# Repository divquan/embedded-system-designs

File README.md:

# embedded-system-designs
This repository contains designs for embedded systems, including schematics, PCB layouts, and fabrication files. Ideal for learning and project inspiration.
# Embedded Systems Design Repository

Welcome to the Embedded Systems Design Repository! This repository contains a comprehensive collection of designs for various embedded systems, including detailed schematics, layouts, and printed circuit board (PCB) designs. Whether you're a beginner looking to learn more about embedded systems or an experienced developer seeking inspiration and reference designs, this repository has something for you.

## Repository Contents

1. **Schematics**
   - Detailed circuit diagrams for different embedded systems projects.
   - Includes component lists, connection details, and annotations to facilitate easy understanding and replication.

2. **PCB Layouts**
   - High-quality PCB layouts ready for fabrication.
   - Gerber files, drill files, and board outlines provided for each project.
   - Layered designs with clear routing paths, power planes, and signal integrity considerations.

3. **Project Documentation**
   - Comprehensive documentation for each project, including design goals, system architecture, and implementation details.
   - Step-by-step guides on assembling and testing the embedded systems.
   - Troubleshooting tips and common issues faced during the development process.

4. **Component Libraries**
   - Custom component libraries for popular PCB design software (e.g., Eagle, KiCad).
   - Includes footprints, 3D models, and symbol libraries for easy integration into your designs.

5. **Example Projects**
   - A variety of example projects demonstrating different aspects of embedded systems design.
   - Projects range from simple microcontroller-based designs to complex multi-component systems.
   - Examples include IoT devices, sensor networks, robotics controllers, and more.

6. **Design Resources**
   - Links to useful resources, such as datasheets, application notes, and design guidelines.
   - Tutorials and educational material to help you get started with embedded systems design.

## How to Use

- **Browse the Projects:** Explore the various projects listed in the repository. Each project folder contains all necessary files and documentation.
- **Clone the Repository:** Use `git clone` to download the repository to your local machine.
- **Open and Modify Designs:** Use your preferred PCB design software to open and modify the schematics and PCB layouts.
- **Fabricate and Assemble:** Use the provided Gerber files to fabricate your PCBs. Follow the assembly guides to build and test your embedded systems.
- **Contribute:** Feel free to contribute to the repository by adding your own designs, improving existing ones, or providing feedback and suggestions.

We hope this repository serves as a valuable resource for your embedded systems design projects. Happy designing!

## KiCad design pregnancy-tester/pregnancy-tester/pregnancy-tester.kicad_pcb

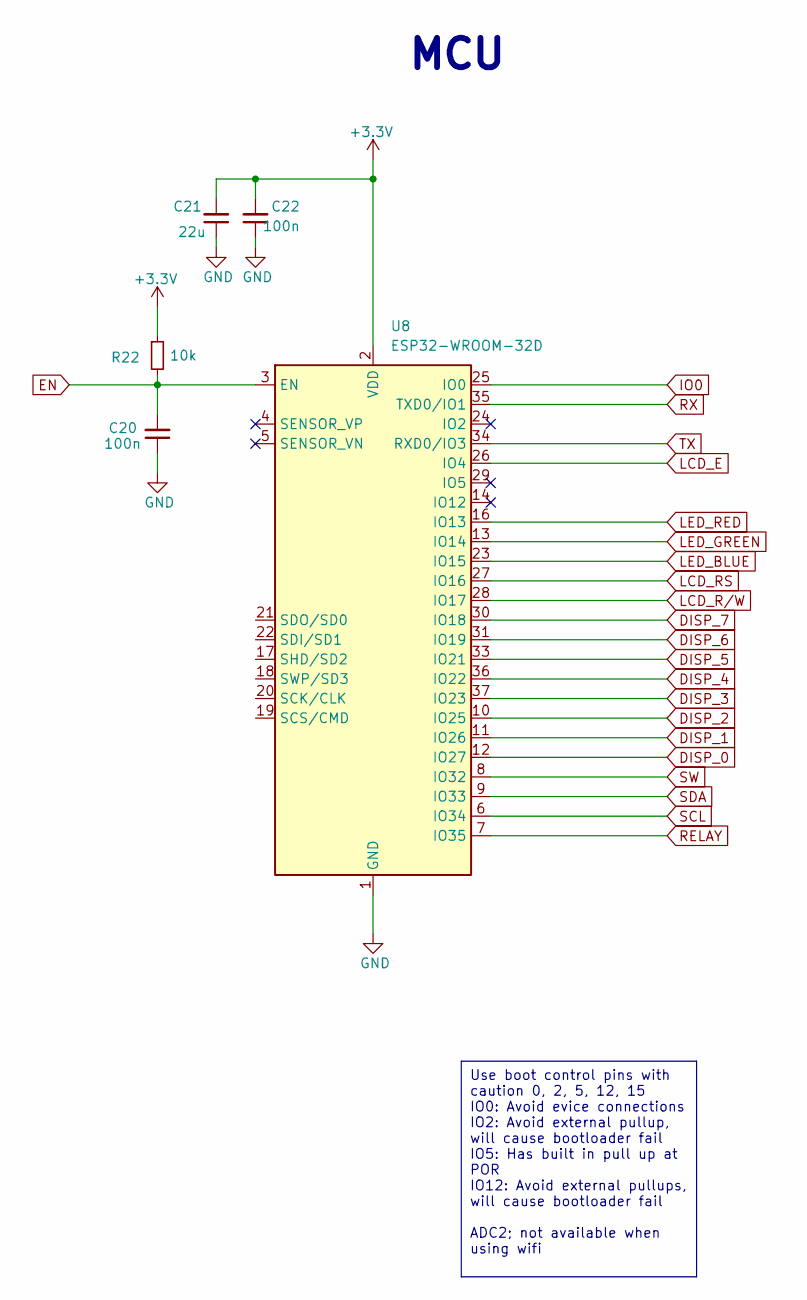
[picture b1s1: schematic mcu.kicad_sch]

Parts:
C20, C22: 100n; C_0201_0603Metric_Pad0.64x0.40mm_HandSolder
C21: 22u; C_01005_0402Metric_Pad0.57x0.30mm_HandSolder
R22: 10k; R_01005_0402Metric_Pad0.57x0.30mm_HandSolder
U8: ESP32-WROOM-32D

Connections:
+3.3V: C20.1, C21.1, C21.2, C22.1, C22.2, R22.1, U8.1 (GND), U8.2 (VDD), U8.15 (GND), U8.38 (GND), U8.39 (GND); also elsewhere on the board
DISP_0: U8.12 (IO27); also elsewhere on the board
DISP_1: U8.11 (IO26); also elsewhere on the board
DISP_2: U8.10 (IO25); also elsewhere on the board
DISP_3: U8.37 (IO23); also elsewhere on the board
DISP_4: U8.36 (IO22); also elsewhere on the board
DISP_5: U8.33 (IO21); also elsewhere on the board
DISP_6: U8.31 (IO19); also elsewhere on the board
DISP_7: U8.30 (IO18); also elsewhere on the board
EN: C20.2, R22.2, U8.3 (EN); also elsewhere on the board
IO0: U8.25 (IO0); also elsewhere on the board
LCD_E: U8.26 (IO4); also elsewhere on the board
LCD_RS: U8.27 (IO16); also elsewhere on the board
LCD_R/W: U8.28 (IO17); also elsewhere on the board
LED_BLUE: U8.23 (IO15)
LED_GREEN: U8.13 (IO14)
LED_RED: U8.16 (IO13)
RELAY: U8.7 (IO35); also elsewhere on the board
RX: U8.35 (TXD0/IO1); also elsewhere on the board
SCL: U8.6 (IO34); also elsewhere on the board
SDA: U8.9 (IO33); also elsewhere on the board
SW: U8.8 (IO32); also elsewhere on the board
TX: U8.34 (RXD0/IO3); also elsewhere on the board

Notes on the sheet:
Use boot control pins with caution 0, 2, 5, 12, 15 IO0: Avoid evice connections IO2: Avoid external pullup, will cause bootloader fail IO5: Has built in pull up at POR IO12: Avoid external pullups, will cause bootloader fail ADC2; not available when using wifi
MCU

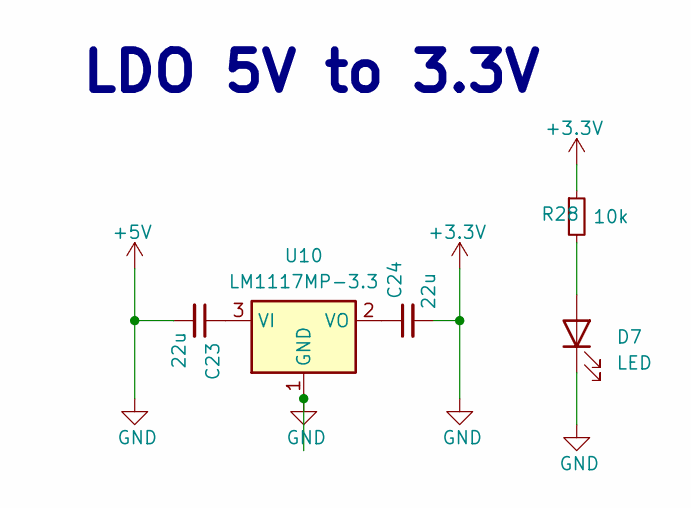
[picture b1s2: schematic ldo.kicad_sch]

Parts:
C23, C24: 22u; C_01005_0402Metric_Pad0.57x0.30mm_HandSolder
D7: LED; LED_0603_1608Metric_Pad1.05x0.95mm_HandSolder
R28: 10k; R_01005_0402Metric_Pad0.57x0.30mm_HandSolder
U10: LM1117MP-3.3; SOT-223-3_TabPin2

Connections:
+3.3V: C23.2, C24.2, D7.1 (K), R28.1, U10.1 (GND); also elsewhere on the board
unnamed: D7.2 (A), R28.2
unnamed: C23.1, U10.3 (VI)
unnamed: C24.1, U10.2 (VO)

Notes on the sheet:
LDO 5V to 3.3V

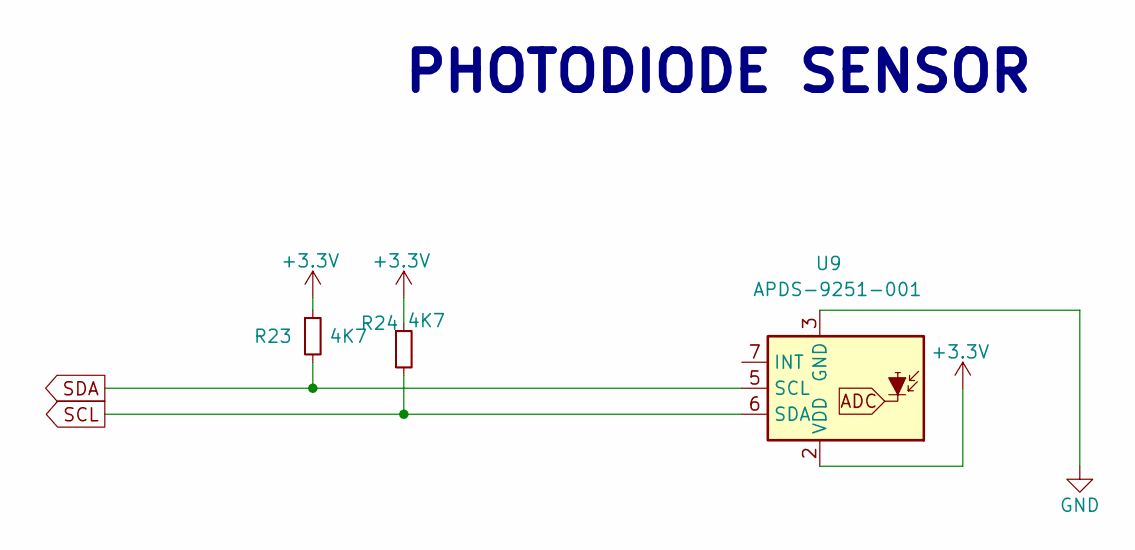
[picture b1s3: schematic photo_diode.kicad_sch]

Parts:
R23, R24: 4K7; R_01005_0402Metric_Pad0.57x0.30mm_HandSolder
U9: APDS-9251-001; Broadcom_LGA-8_2x2mm_P0.5mm

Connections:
+3.3V: R23.1, R24.1, U9.2 (VDD), U9.3 (GND); also elsewhere on the board
SCL: R24.2, U9.6 (SDA); also elsewhere on the board
SDA: R23.2, U9.5 (SCL); also elsewhere on the board

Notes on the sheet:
PHOTODIODE SENSOR

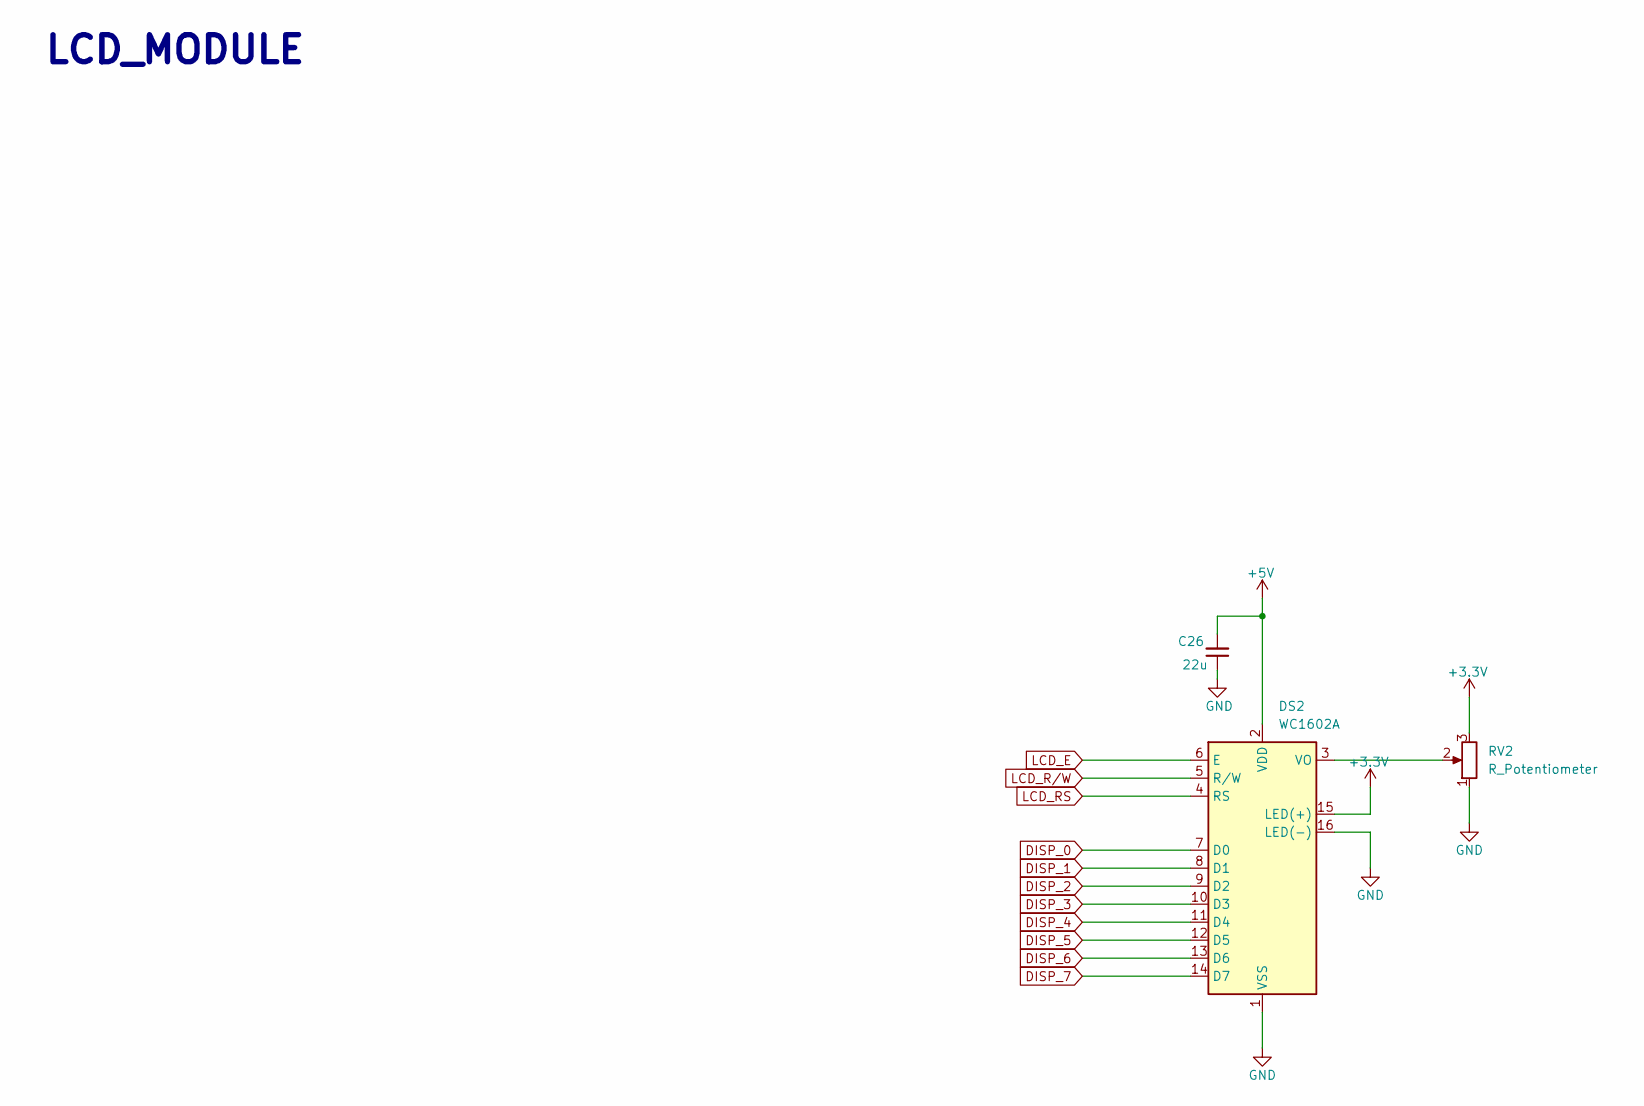
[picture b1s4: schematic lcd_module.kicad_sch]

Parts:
C26: 22u; C_01005_0402Metric_Pad0.57x0.30mm_HandSolder
DS2: WC1602A
RV2: R_Potentiometer; Potentiometer_ACP_CA14-VSMD_Vertical_Hole

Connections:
+3.3V: C26.1, C26.2, DS2.1 (VSS), DS2.2 (VDD), DS2.15 (LED(+)), DS2.16 (LED(-)), RV2.1, RV2.3; also elsewhere on the board
DISP_0: DS2.7 (D0); also elsewhere on the board
DISP_1: DS2.8 (D1); also elsewhere on the board
DISP_2: DS2.9 (D2); also elsewhere on the board
DISP_3: DS2.10 (D3); also elsewhere on the board
DISP_4: DS2.11 (D4); also elsewhere on the board
DISP_5: DS2.12 (D5); also elsewhere on the board
DISP_6: DS2.13 (D6); also elsewhere on the board
DISP_7: DS2.14 (D7); also elsewhere on the board
LCD_E: DS2.6 (E); also elsewhere on the board
LCD_RS: DS2.4 (RS); also elsewhere on the board
LCD_R/W: DS2.5 (R/W); also elsewhere on the board
unnamed: DS2.3 (VO), RV2.2

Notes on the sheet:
LCD_MODULE

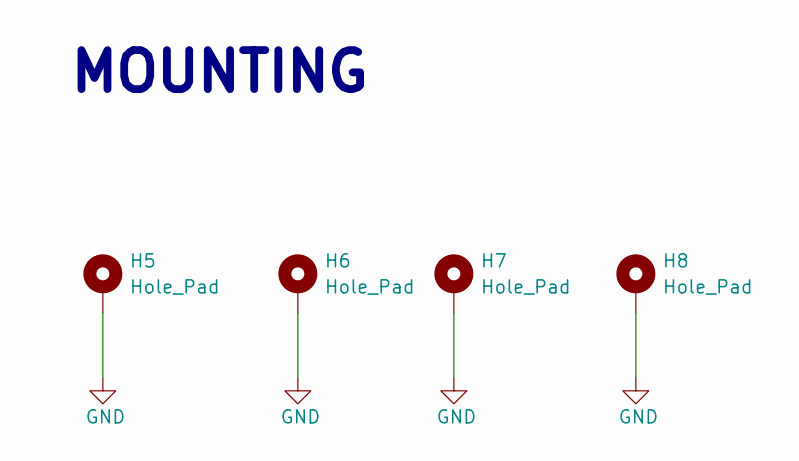
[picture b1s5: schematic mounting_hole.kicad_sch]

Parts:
H5, H6, H7, H8: Hole_Pad; MountingHole_2.2mm_M2_DIN965_Pad

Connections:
+3.3V: H5.1, H6.1, H7.1, H8.1; also elsewhere on the board

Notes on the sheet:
MOUNTING

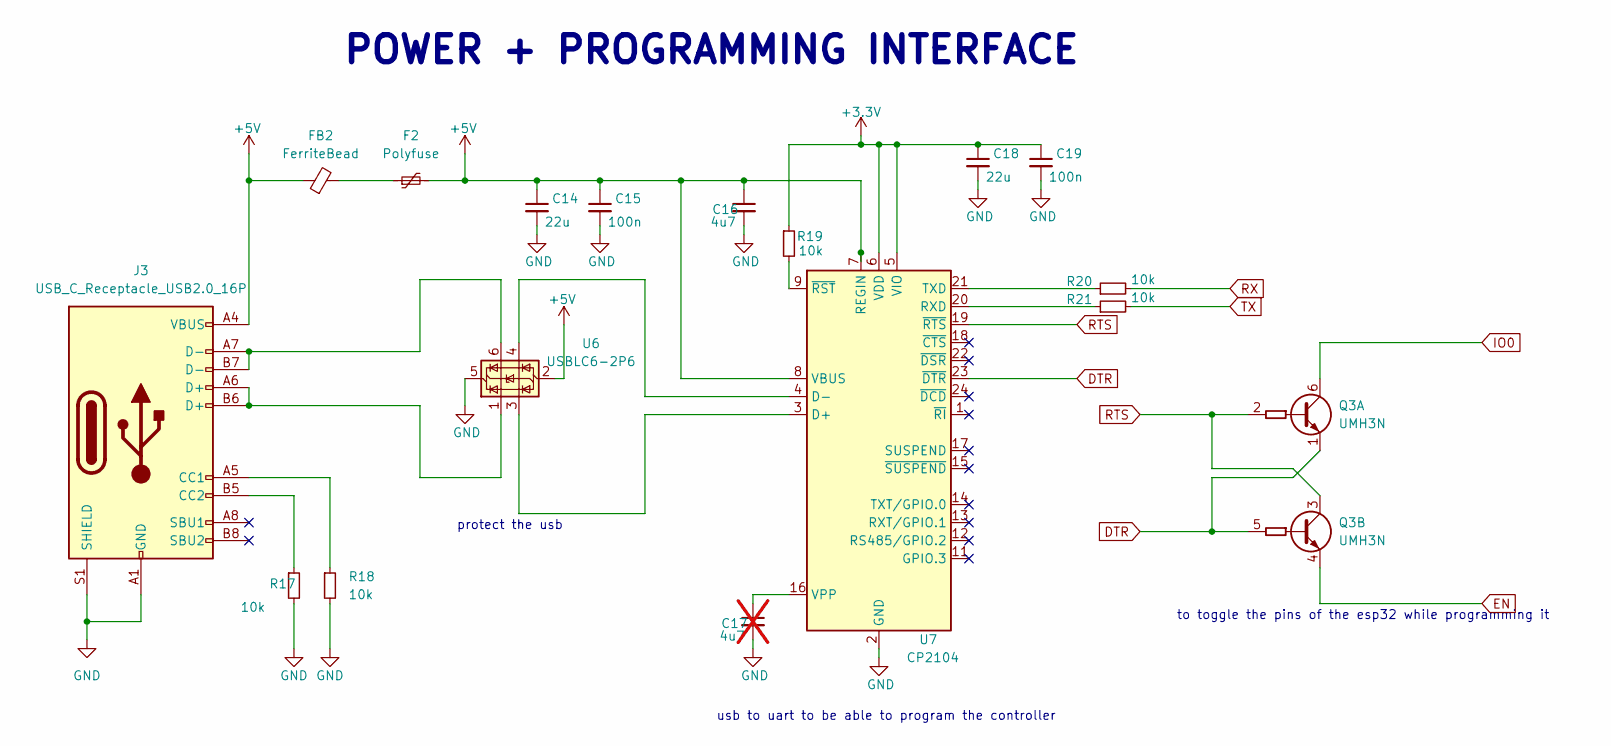
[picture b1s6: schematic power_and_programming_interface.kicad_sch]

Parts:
C14, C18: 22u; C_01005_0402Metric_Pad0.57x0.30mm_HandSolder
C15, C19: 100n; C_0201_0603Metric_Pad0.64x0.40mm_HandSolder
C16: 4u7; C_0805_2012Metric_Pad1.18x1.45mm_HandSolder
C17: 4u7; C_01005_0402Metric_Pad0.57x0.30mm_HandSolder; not fitted
F2: Polyfuse; Fuse_Bourns_MF-RG500
FB2: FerriteBead; L_0603_1608Metric_Pad1.05x0.95mm_HandSolder
J3: USB_C_Receptacle_USB2.0_16P; USB_C_Receptacle_HRO_TYPE-C-31-M-12
Q3: UMH3N; SOT-363_SC-70-6
R17, R18, R19, R20, R21: 10k; R_01005_0402Metric_Pad0.57x0.30mm_HandSolder
U6: USBLC6-2P6; SOT-666
U7: CP2104; QFN-24-1EP_4x4mm_P0.5mm_EP2.6x2.6mm

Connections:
+3.3V: C14.1, C14.2, C15.1, C15.2, C16.1, C16.2, C17.2, C18.1, C18.2, C19.1, C19.2, F2.2, FB2.1, J3.A1 (GND), J3.A4 (VBUS), J3.A9 (VBUS), J3.A12 (GND), J3.B1 (GND), J3.B4 (VBUS), J3.B9 (VBUS), J3.B12 (GND), J3.S1 (SHIELD), R17.2, R18.2, R19.1, U6.2 (GND), U6.5 (VBUS), U7.2 (GND), U7.5 (VIO), U7.6 (VDD), U7.7 (REGIN), U7.8 (VBUS), U7.25 (GND); also elsewhere on the board
DTR: Q3.1 (E1), Q3.5 (B2), U7.23 (~DTR)
EN: Q3.4 (E2); also elsewhere on the board
IO0: Q3.6 (C1); also elsewhere on the board
unnamed: F2.1, FB2.2
unnamed: J3.A5 (CC1), R18.1
unnamed: J3.B5 (CC2), R17.1
unnamed: J3.A6 (D+), J3.B6 (D+), U6.1 (I/O1)
unnamed: J3.A7 (D-), J3.B7 (D-), U6.6 (I/O1)
unnamed: U6.3 (I/O2), U7.3 (D+)
unnamed: U6.4 (I/O2), U7.4 (D-)
unnamed: R21.1, U7.20 (RXD)
unnamed: R20.1, U7.21 (TXD)
unnamed: C17.1, U7.16 (VPP)
unnamed: R19.2, U7.9 (~RST)
RTS: Q3.2 (B1), Q3.3 (C2), U7.19 (~RTS)
RX: R20.2; also elsewhere on the board
TX: R21.2; also elsewhere on the board

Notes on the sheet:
usb to uart to be able to program the controller
to toggle the pins of the esp32 while programming it
protect the usb
POWER + PROGRAMMING INTERFACE

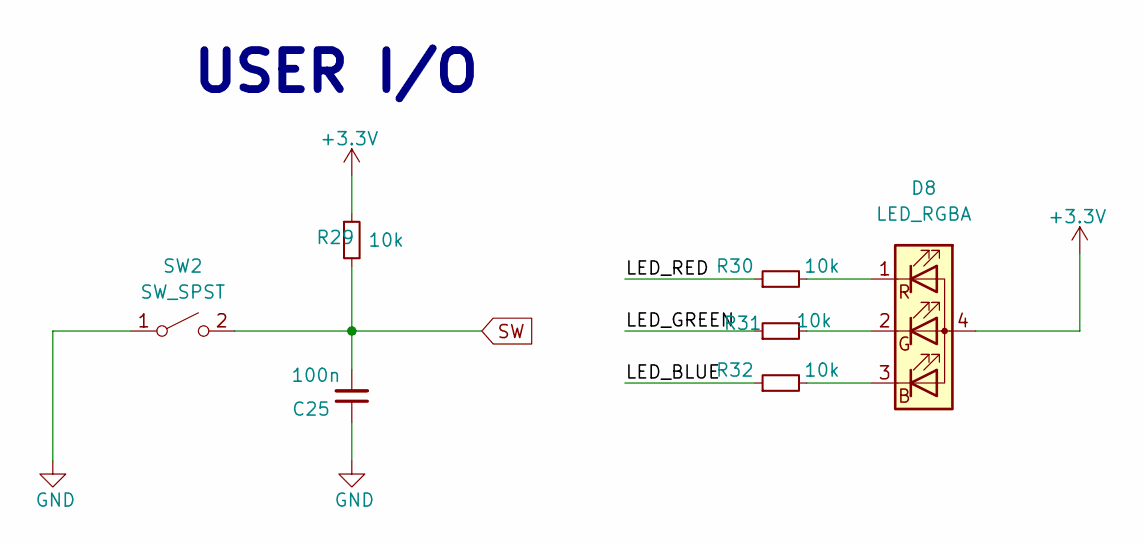
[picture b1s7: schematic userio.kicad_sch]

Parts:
C25: 100n; C_0201_0603Metric_Pad0.64x0.40mm_HandSolder
D8: LED_RGBA; LED_RGB_Wuerth-PLCC4_3.2x2.8mm_150141M173100
R29, R30, R31, R32: 10k; R_01005_0402Metric_Pad0.57x0.30mm_HandSolder
SW2: SW_SPST; SW_PUSH_1P1T_6x3.5mm_H4.3_APEM_MJTP1243

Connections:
+3.3V: C25.1, D8.4 (A), R29.1, SW2.1 (A); also elsewhere on the board
/User_IO/LED_BLUE: R32.1
/User_IO/LED_GREEN: R31.1
/User_IO/LED_RED: R30.1
unnamed: D8.3 (BK), R32.2
unnamed: D8.2 (GK), R31.2
unnamed: D8.1 (RK), R30.2
SW: C25.2, R29.2, SW2.2 (B); also elsewhere on the board

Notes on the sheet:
USER I/O

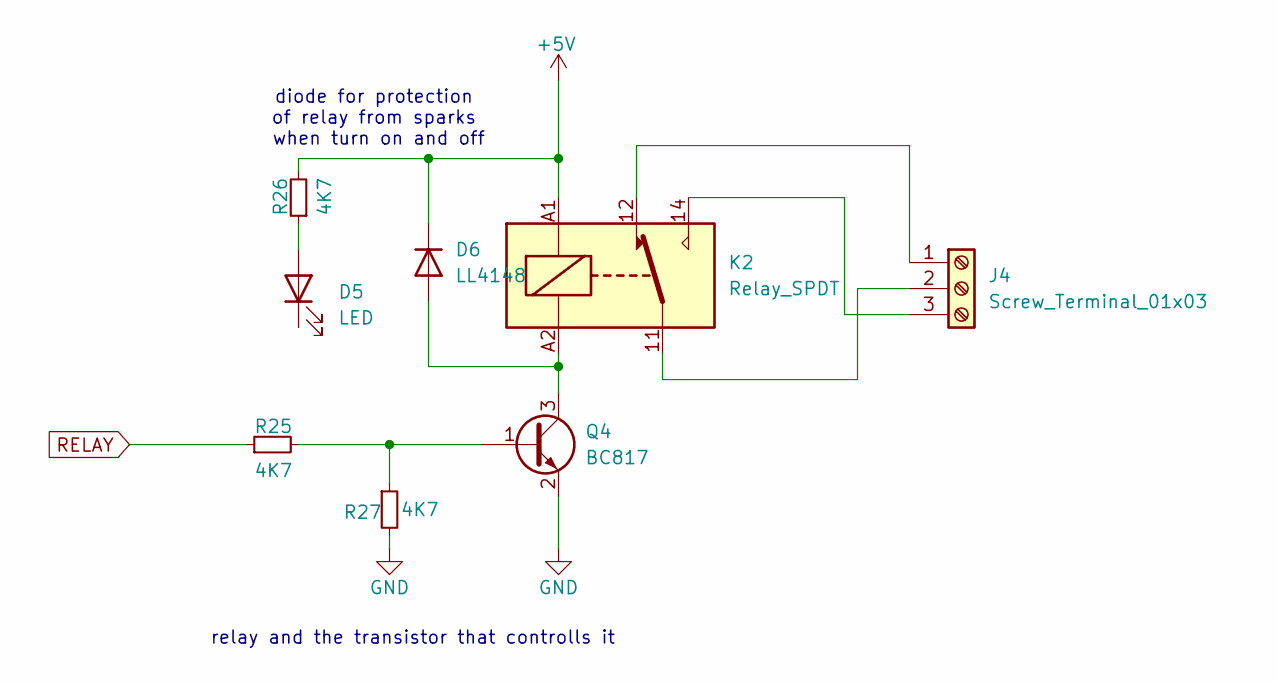
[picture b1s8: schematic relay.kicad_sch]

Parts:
D5: LED; LED_0603_1608Metric_Pad1.05x0.95mm_HandSolder
D6: LL4148; D_MiniMELF_Handsoldering
J4: Screw_Terminal_01x03; TerminalBlock_Phoenix_PTSM-0,5-3-2.5-V-THR_1x03_P2.50mm_Ver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
K2: Relay_SPDT; Relay_SPDT_Schrack-RT1-16A-FormC_RM5mm
Q4: BC817; SOT-23
R25, R26, R27: 4K7; R_01005_0402Metric_Pad0.57x0.30mm_HandSolder

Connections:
+3.3V: D6.1 (K), K2.A1, Q4.2 (E), R26.2, R27.2; also elsewhere on the board
unnamed: D5.2 (A), R26.1
unnamed: D6.2 (A), K2.A2, Q4.3 (C)
unnamed: J4.1, K2.12
unnamed: J4.2, K2.11
unnamed: J4.3, K2.14
unnamed: Q4.1 (B), R25.2, R27.1
RELAY: R25.1; also elsewhere on the board

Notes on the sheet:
diode for protection of relay from sparks when turn on and off
relay and the transistor that controlls it

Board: 2 copper layers, 52 parts (0 on the bottom side), 46 nets, no tracks yet.

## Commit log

2024-06-15 Added Untitled Diagram.drawio
2024-06-15 add generic components after brainstorming
2024-06-17 diagram: modifie
2024-06-17 diagram: modify brainstorming to include specification
2024-06-17 modify: rename pregnancy tester diagram
2024-06-21 added all components
